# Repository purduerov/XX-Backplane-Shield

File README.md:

# XX-Backplane-Shield

This board will contain the raspberry pi 3 and act as a mounting point onto the electrnoic enclosure which will be mount horrizontally. The board will attach the IMU and the bluerobotics pressure sensor.

The raspberry pi will need an ethernet and usb cammeras plugged into it, so the size of the board was kept at a minimum to make working with wires easier.

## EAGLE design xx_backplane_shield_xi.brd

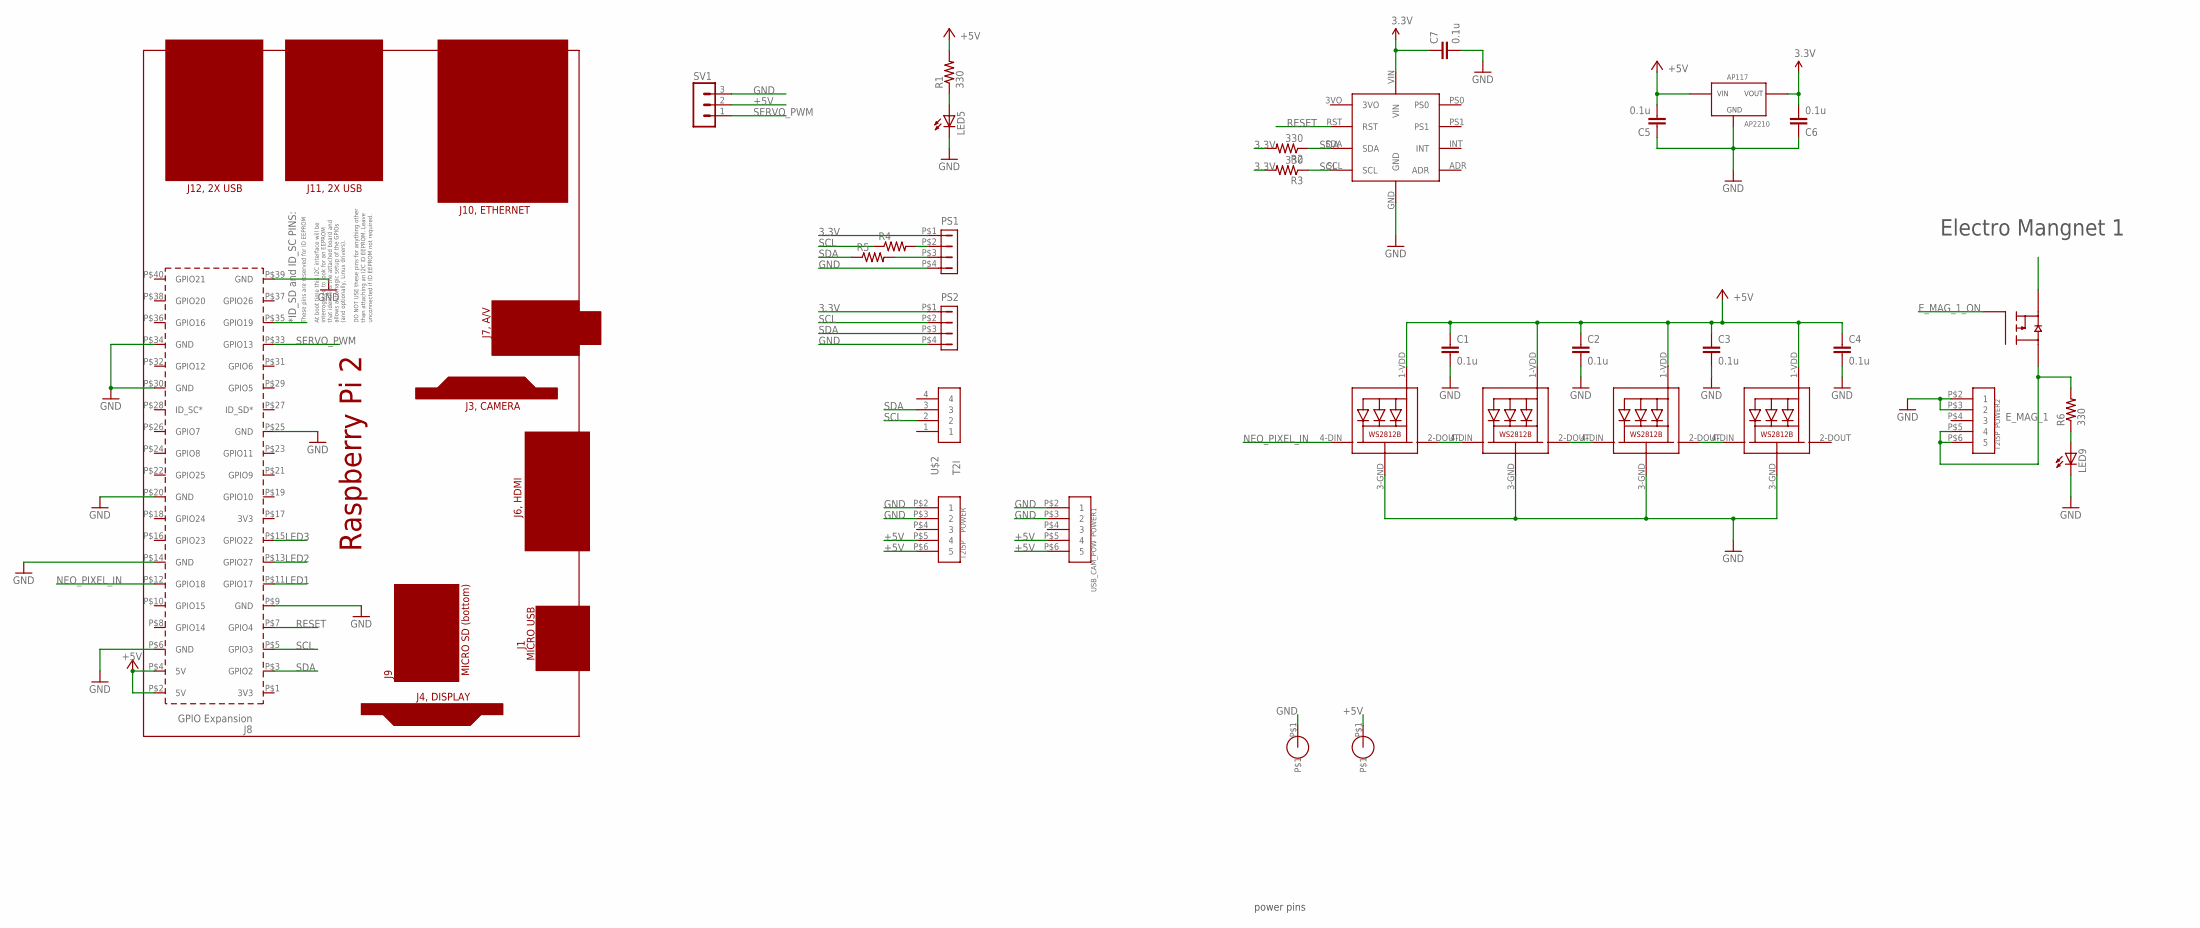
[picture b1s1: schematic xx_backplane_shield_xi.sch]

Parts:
C1, C2, C3, C4, C5, C6, C7: 0.1u; 0603-CAP
LED1, LED2, LED3, LED4: WS2812B5050; WS2812B
LED5, LED9: LEDSML0603; SML0603
PCB1: RPI2
POWER, POWER2: T2I5P
POWER1: USB_CAM_POW; T2I5P
PS1, PS2: DF13-4P-1.25DSA
R1, R2, R3, R6: 330; R0603
R4: 0 Ohms; R0603
R5: 0 ohms; R0603
SV1: MA03-1
U1: FQB27P06; TO263-3
U$2: T2I
U$3: BNO055_9DOF_BREAKOUT; BNO055
U$4, U$6: THROUGHOLE; THROUGHHOLE
U$5: AP2210; SOT-23-3

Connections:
3.3V: C6.2, C7.1, PS1.P$1 (1), PS2.P$1 (1), R2.2, R3.2, U$3.VIN, U$5.VOUT
+5V: C1.1, C2.1, C3.1, C4.1, C5.2, LED1.1-VDD (VDD), LED2.1-VDD (VDD), LED3.1-VDD (VDD), LED4.1-VDD (VDD), PCB1.P$2 (5V), PCB1.P$4 (5V), POWER.P$5 (4), POWER.P$6 (5), POWER1.P$5 (4), POWER1.P$6 (5), R1.2, SV1.2, U1.3 (S2), U$4.P$1, U$5.VIN
E_MAG_1: POWER2.P$5 (4), POWER2.P$6 (5), R6.2, U1.TAB (D2)
E_MAG_1_ON: PCB1.P$35 (GPIO19), U1.1 (G2)
GND: C1.2, C2.2, C3.2, C4.2, C5.1, C6.1, C7.2, LED1.3-GND (GND), LED2.3-GND (GND), LED3.3-GND (GND), LED4.3-GND (GND), LED5.C, LED9.C, PCB1.P$6 (GND), PCB1.P$9 (GND), PCB1.P$14 (GND), PCB1.P$20 (GND), PCB1.P$25 (GND), PCB1.P$30 (GND), PCB1.P$34 (GND), PCB1.P$39 (GND), POWER.P$2 (1), POWER.P$3 (2), POWER1.P$2 (1), POWER1.P$3 (2), POWER2.P$2 (1), POWER2.P$3 (2), PS1.P$4 (4), PS2.P$4 (4), SV1.3, U$3.GND, U$5.GND, U$6.P$1
LED1: PCB1.P$11 (GPIO17)
LED2: PCB1.P$13 (GPIO27)
LED3: PCB1.P$15 (GPIO22)
unnamed: PS1.P$2 (2), R4.2
unnamed: LED5.A, R1.1
unnamed: LED1.2-DOUT (DO), LED2.4-DIN (DI)
unnamed: LED2.2-DOUT (DO), LED3.4-DIN (DI)
unnamed: LED3.2-DOUT (DO), LED4.4-DIN (DI)
unnamed: PS1.P$3 (3), R5.2
unnamed: LED9.A, R6.1
NEO_PIXEL_IN: LED1.4-DIN (DI), PCB1.P$12 (GPIO18)
RESET: PCB1.P$7 (GPIO4), U$3.RST
SCL: PCB1.P$5 (GPIO3), PS2.P$2 (2), R3.1, R4.1, U$2.2, U$3.SCL
SDA: PCB1.P$3 (GPIO2), PS2.P$3 (3), R2.1, R5.1, U$2.3, U$3.SDA
SERVO_PWM: PCB1.P$33 (GPIO13), SV1.1

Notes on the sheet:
power pins
Electro Mangnet 1

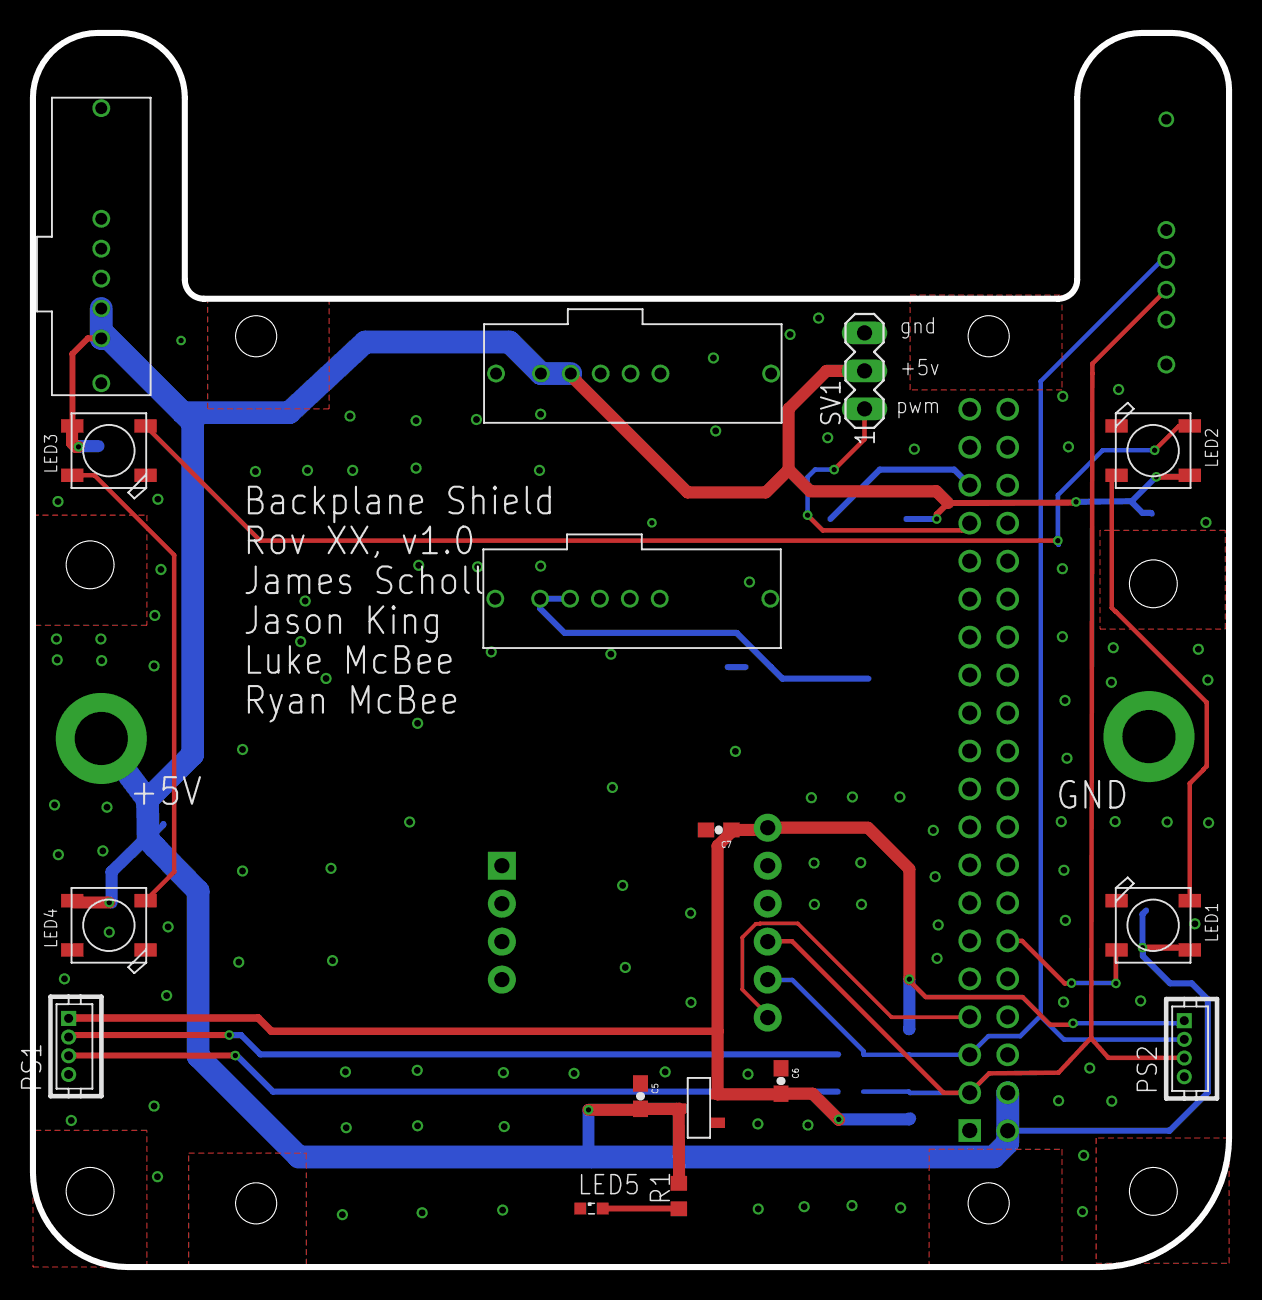
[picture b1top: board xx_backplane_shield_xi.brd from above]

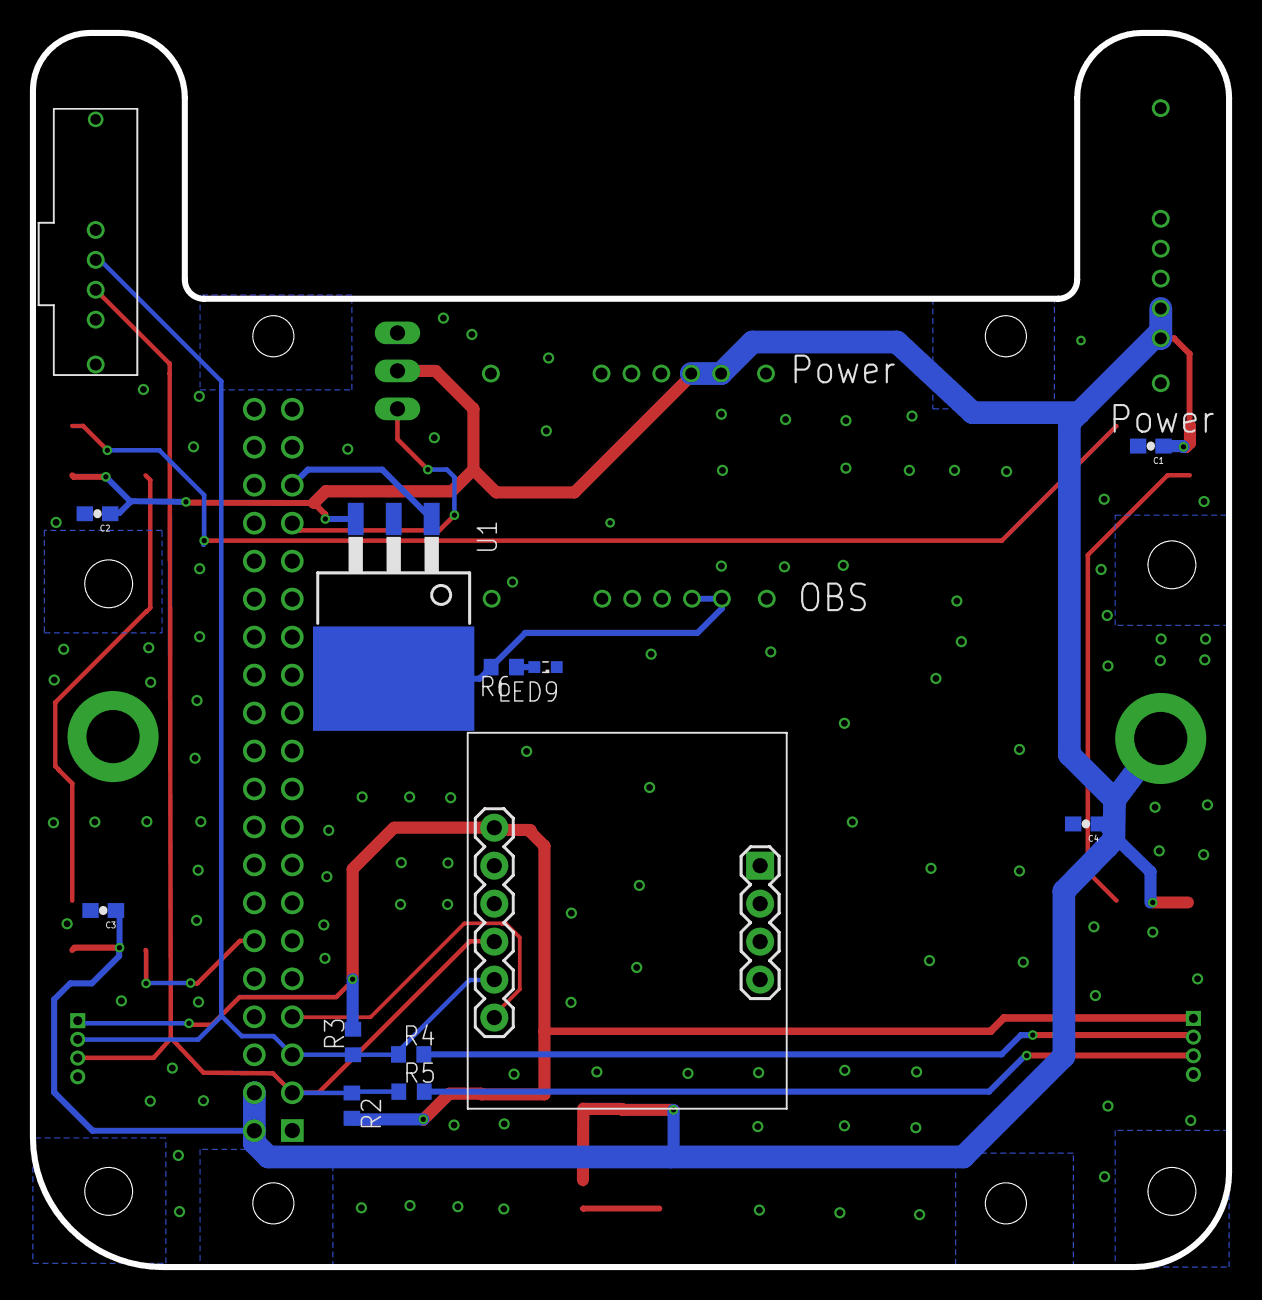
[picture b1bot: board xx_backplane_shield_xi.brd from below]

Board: 2 copper layers, 80.0 x 82.5 mm, 32 parts (14 on the bottom side), 17 nets.

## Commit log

2017-10-14 new shield in progress
2017-10-14 Cleaning up eagle file and renaming board name
2017-10-15 Added gitignore
2017-10-15 Removed unnecessary temp files
2017-10-20 deleted like everything
2017-12-07 finished board version 1
2017-12-30 part placement almost done
2017-12-30 half way done routing first revision
2017-12-30 finished routing, need to add final touches
2018-01-04 updating the readme
2018-01-06 made the fixes
2018-01-06 removing a few vias from my name
2018-01-07 Updated traces and changed connector for main camera
2018-01-07 Removed some vias, board was ugly
2018-01-07 Added silkscreen
2018-01-07 Fixed silkscreen layer
2018-01-08 Added connector and mosfet for OBS
2018-01-10 Version submitted to elecrow
2018-02-15 Added servo motor connection

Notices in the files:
parts and their libraries:
SparkFun-Passives: Licensing: Creative Commons ShareAlike 4.0 International - https://creativecommons.org/licenses/by-sa/4.0
